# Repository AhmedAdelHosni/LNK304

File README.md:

[28.Sep.2017]
The board was tested in April 2016 and there was a missing connector. After fixing it, the board did not behave as required. 
The project is Obselete now.

# LNK304
AC to DC converter from 220v to 9v using LNK304 desing. This design in still in testing phase

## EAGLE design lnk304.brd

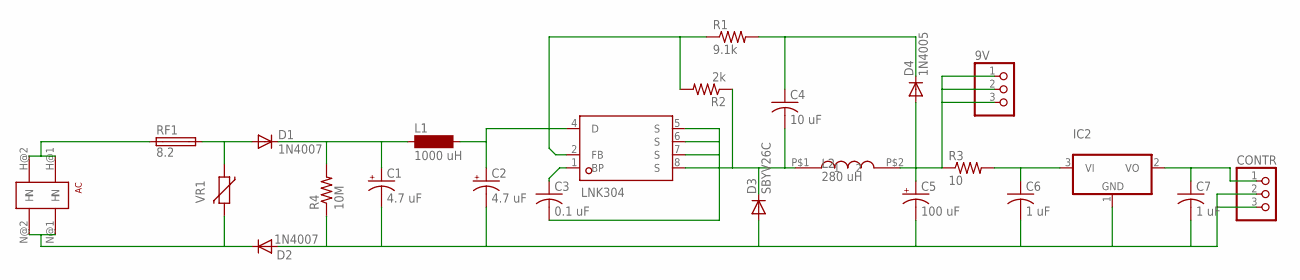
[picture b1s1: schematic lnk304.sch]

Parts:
9V: PINHD-1X3; 1X03
AC: TBLOCK02X2
C1, C2: 4.7 uF; E5-10,5
C3: 0.1 uF; C0603
C4: 10 uF; C0603
C5: 100 uF; E2-4
C6, C7: 1 uF; C0603
CONTR: PINHD-1X3; 1X03
D1, D2: 1N4007; DO41-10
D3: SBYV26C; DO41-10
D4: 1N4005; DO41-10
IC2: MCP1703CB; SOT23
L1: 1000 uH; BS11
L2: 280 uH; ELL-6UH681M
LNK304: LNK30X; SO08C
R1: 9.1k; R0603
R2: 2k; R0603
R3: 10; R1206
R4: 10M; R1206
RF1: 8.2; PICOFUSE
VR1: VARISTOR-7,5; R-7,5

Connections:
GND: C1.-, C2.-, C5.-, C6.2, C7.2, CONTR.2, CONTR.3, D2.A, D3.A, IC2.1 (GND), R4.1
unnamed: D1.A, RF1.2, VR1.1
unnamed: C1.+, D1.C, L1.1, R4.2
unnamed: C2.+, L1.2, LNK304.4 (D)
unnamed: 9V.1, 9V.2, 9V.3, C5.+, D4.A, L2.P$2 (2), R3.1
unnamed: LNK304.2 (FB), R1.1, R2.2
unnamed: AC.N@1 (N), AC.N@2 (N), D2.C, VR1.2
unnamed: C3.1, LNK304.1 (BP)
unnamed: C3.2, C4.2, D3.C, L2.P$1 (1), LNK304.5 (S), LNK304.6 (S), LNK304.7 (S), LNK304.8 (S), R2.1
unnamed: C4.1, D4.C, R1.2
unnamed: C6.1, IC2.3 (VI), R3.2
unnamed: AC.H@1 (H), AC.H@2 (H), RF1.1
unnamed: C7.1, CONTR.1, IC2.2 (VO)

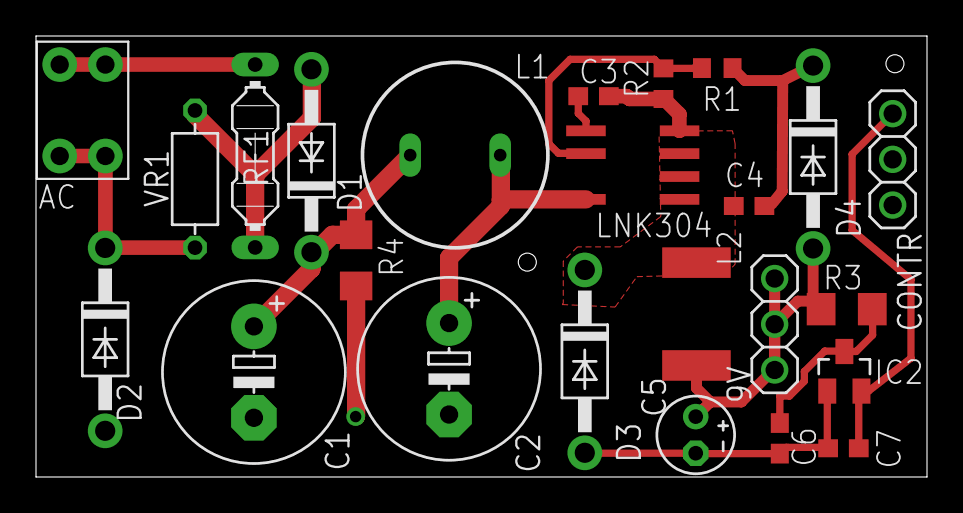
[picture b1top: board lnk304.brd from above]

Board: 2 copper layers, 49.5 x 24.5 mm, 24 parts (0 on the bottom side), 13 nets.

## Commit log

2016-03-13 :octocat: Added .gitattributes & .gitignore files
2016-03-13 README.md
2016-03-13 LNK304 V1.0
    This design aim to convert 220v to 9v using the LNK304.
    This version is first prototype for a pcb layout and will be upgraded
    later.
2016-03-19 Add new document "Board Analysis.txt"
    This file includes the history of the the analysis for the PCB layout
    design + taking into consideration the size of the Controller and the
    relay boards.
    This version includes initial measurements.
2016-03-19 Categories the template "Height, Width and Length"
    Categories the template and divide it into sub chapters
    "Height, Width and Length"
2016-03-19 Redesign to add Controller above the converter using pin headers
    ** 19.Mar.2016 **
    Schematic:
    - Change RF1 to fuse component
    - Added Controller pin headers
    PCB Layout:
    - Increase board length from 46mm to 49.5mm
2016-03-19 Add file history.txt
2016-03-21 Added 9v output pins
    ** 21.Mar.2016 **
    Schematic:
    - Added pin headers for 9v output which will be used by the relays
    - Added extra ground pin to CONTR component
    PCB Layout:
    - Added pin headers for 9v output which will be used by the relays
2016-03-26 Added the new package LNK30X
    ** 26.Mar.2016 **
    - Checked in new file userdefined.lbr
    - Created new device LNK30X
    - The device has Symbol name LNK30X
    - The device has Package name SO08C
    Schematic:
2016-03-26 Added Bleeder resistor and varistor
    ** 26.Mar.2016 **
    Schematic:
    - Added a 1M 1/4Watt beelding resistor between hot and neutral
    - Added Varistor VR1
    PCB Layout:
    - Change board height to 49.5mm
2016-03-27 Added passive componets' values which were removed by mistake
    ** 27.Mar.2016 **
    Schematic:
    - Added passive componets' values which were removed by mistake
    PCB Layout:
    - Smash passive components and remove passive components' values
    -- Missing --
2016-04-08 Create new PCB layout for AC TBlock and L2
    ** 8.Apr.2016 **
    Created new devices in the library
    Schematic:
    - Created new library for AC plug
    - Added hot and neutral pins for AC plug concept
    PCB Layout:
2016-05-14 Adding BOM
2016-05-14 Add CERN v1.2 license files
2016-05-14 Adding BOM in .xls extension
